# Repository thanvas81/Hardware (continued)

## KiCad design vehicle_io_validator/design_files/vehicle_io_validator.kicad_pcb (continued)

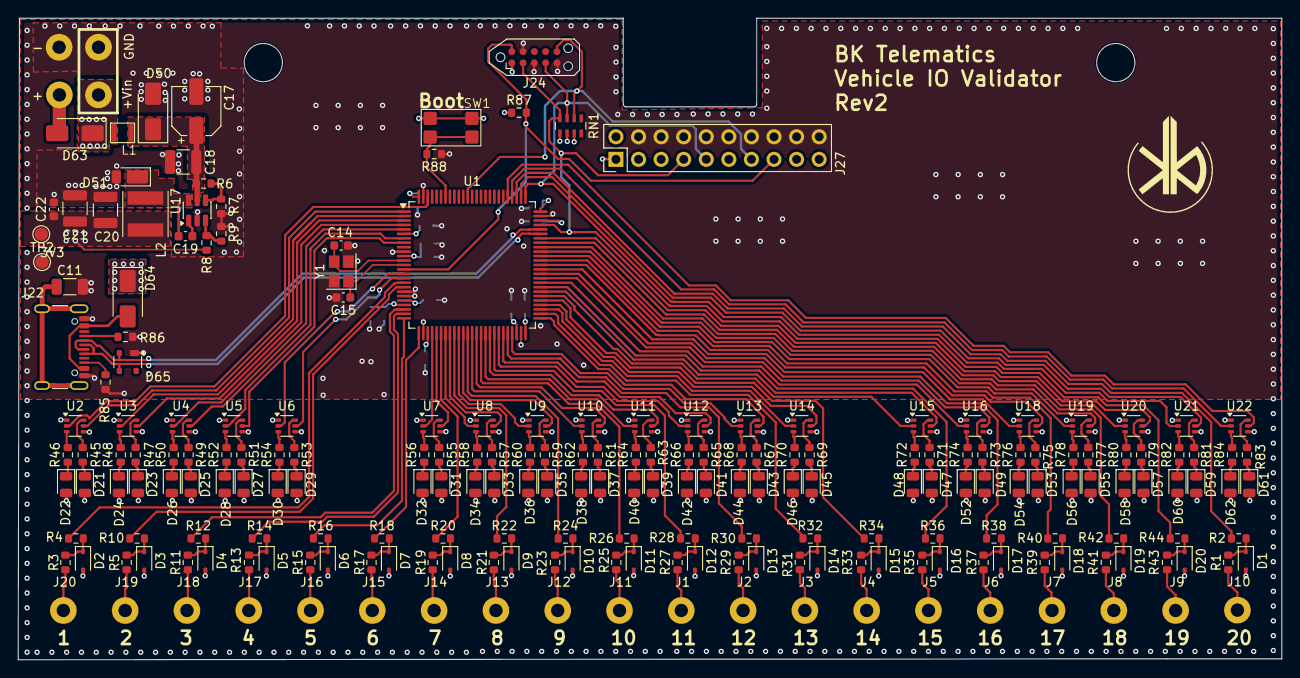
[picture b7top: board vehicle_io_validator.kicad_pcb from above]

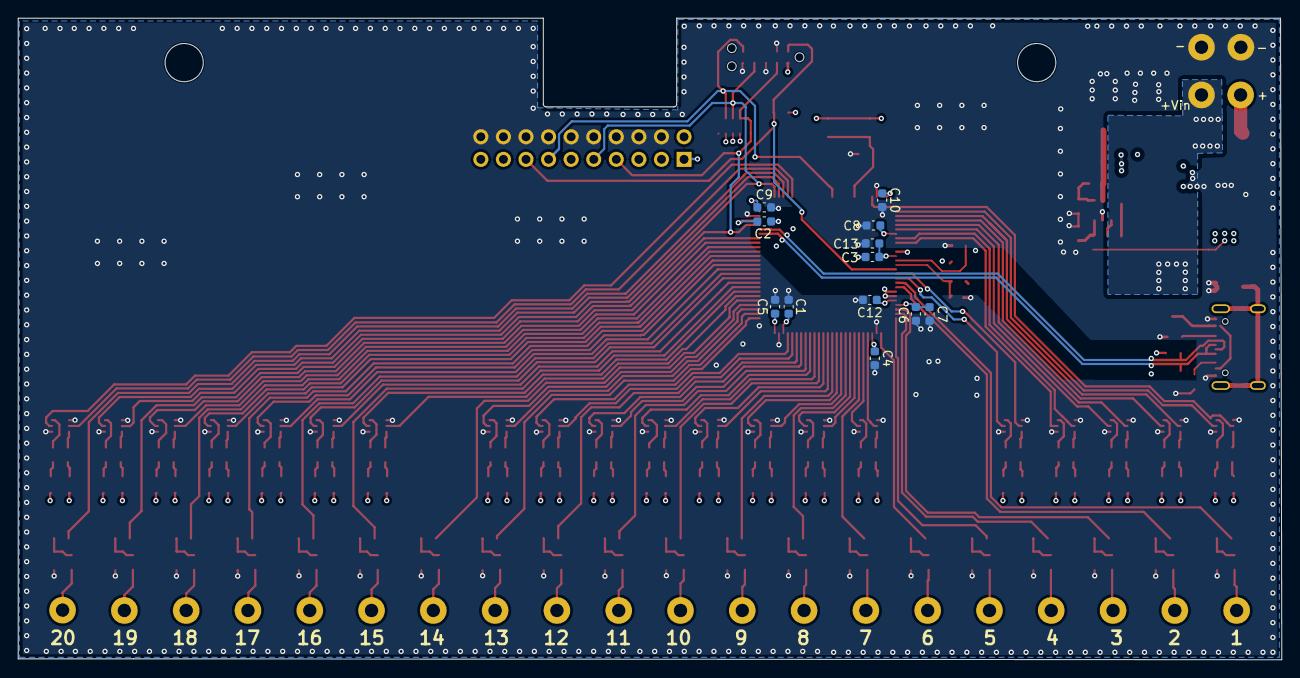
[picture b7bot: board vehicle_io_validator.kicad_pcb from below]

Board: 4 copper layers, 142.1 x 72.2 mm, 232 parts (12 on the bottom side), 201 nets.

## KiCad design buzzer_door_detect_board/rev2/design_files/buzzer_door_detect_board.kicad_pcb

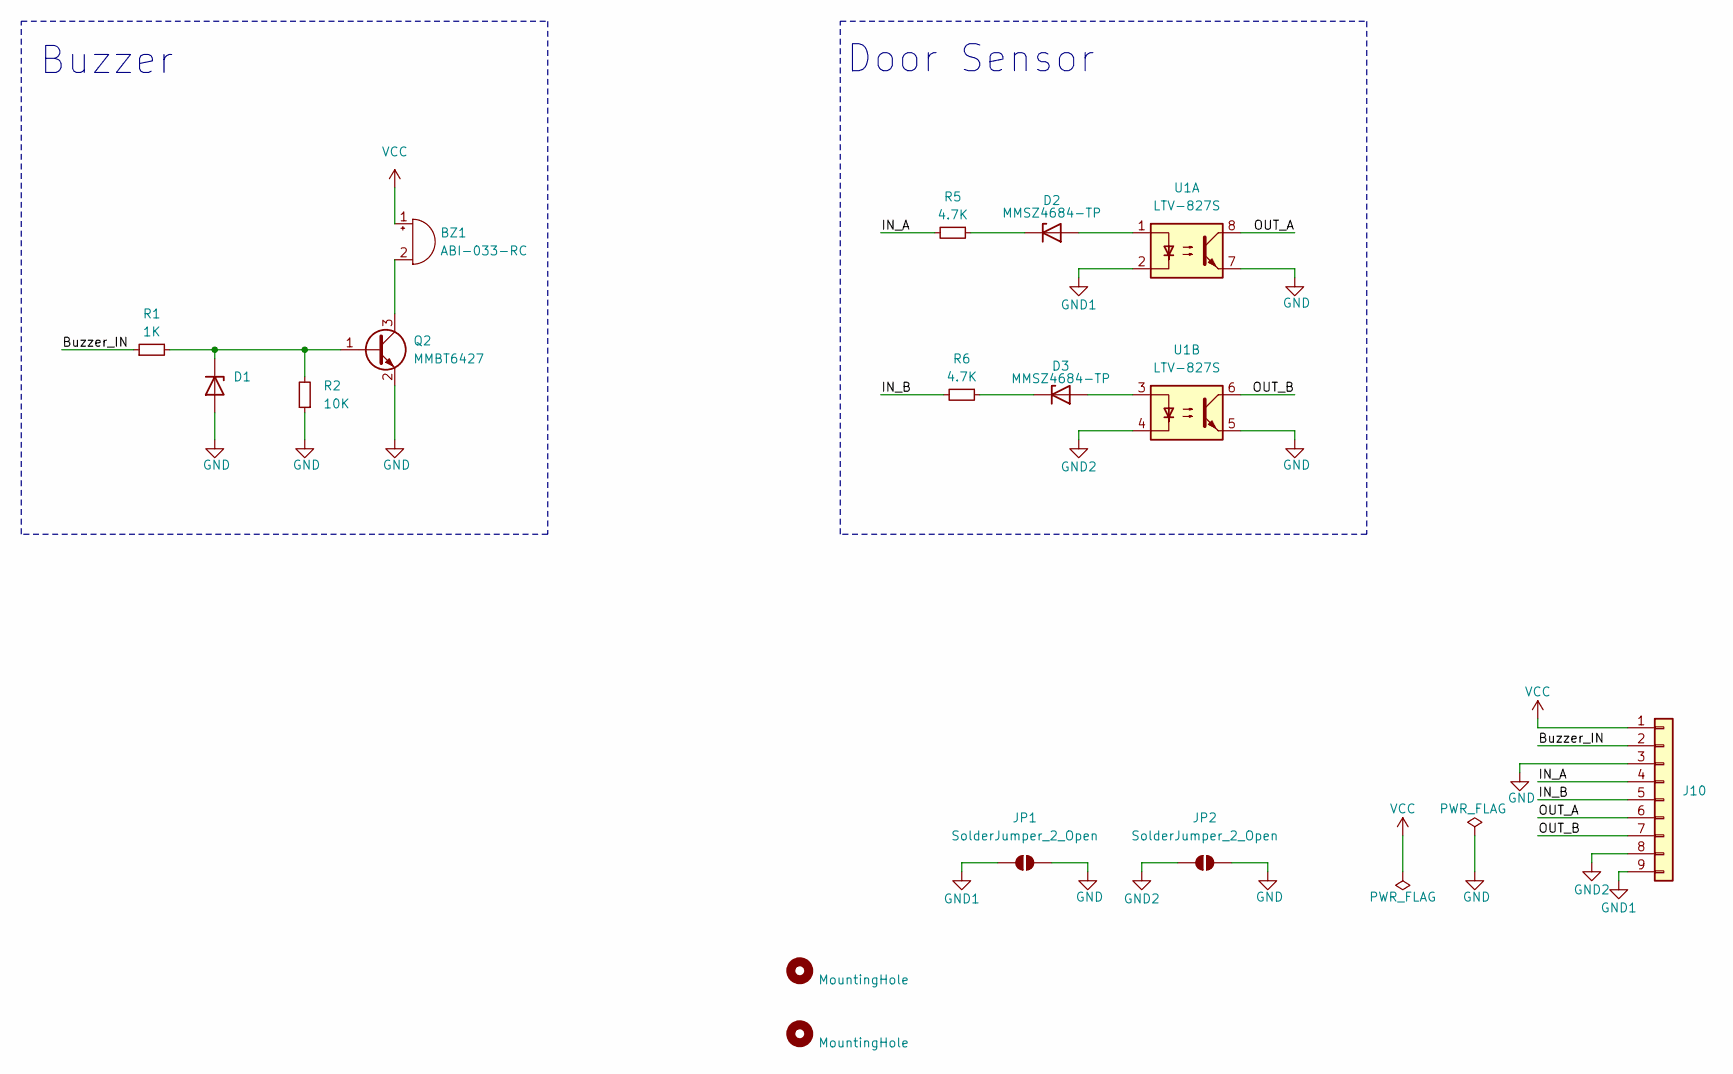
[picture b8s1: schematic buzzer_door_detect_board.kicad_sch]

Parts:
BZ1: ABI-033-RC
D1, D2, D3: MMSZ4684-TP; D_SOD-123
H1, H2: MountingHole; MountingHole_3.2mm_M3
J10: Conn_01x09; JST_ZH_B9B-ZR_1x09_P1.50mm_Vertical
JP1, JP2: SolderJumper_2_Open; SolderJumper-2_P1.3mm_Open_RoundedPad1.0x1.5mm
Q2: MMBT6427; SOT-23
R1: 1K; R_0805_2012Metric
R2: 10K; R_0805_2012Metric
R5, R6: 4.7K; R_0805_2012Metric
U1: LTV-827S; SMDIP-8_W9.53mm

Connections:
/Buzzer_IN: J10.2, R1.1
/IN_A: J10.4, R5.2
/IN_B: J10.5, R6.2
/OUT_A: J10.6, U1.8
/OUT_B: J10.7, U1.6
GND: D1.2 (A), J10.3, JP1.2 (B), JP2.2 (B), Q2.2 (E), R2.1, U1.5, U1.7
GND1: J10.9, JP1.1 (A), U1.2
GND2: J10.8, JP2.1 (A), U1.4
unnamed: BZ1.2 (-), Q2.3 (C)
unnamed: D1.1 (K), Q2.1 (B), R1.2, R2.2
unnamed: D2.2 (A), U1.1
unnamed: D2.1 (K), R5.1
unnamed: D3.2 (A), U1.3
unnamed: D3.1 (K), R6.1
VCC: BZ1.1 (+), J10.1

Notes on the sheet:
Door Sensor
Buzzer

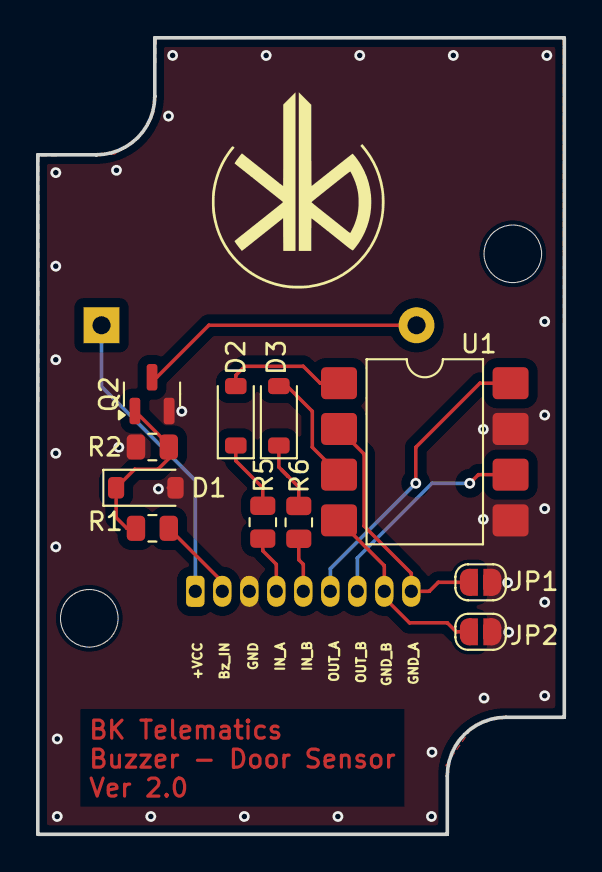
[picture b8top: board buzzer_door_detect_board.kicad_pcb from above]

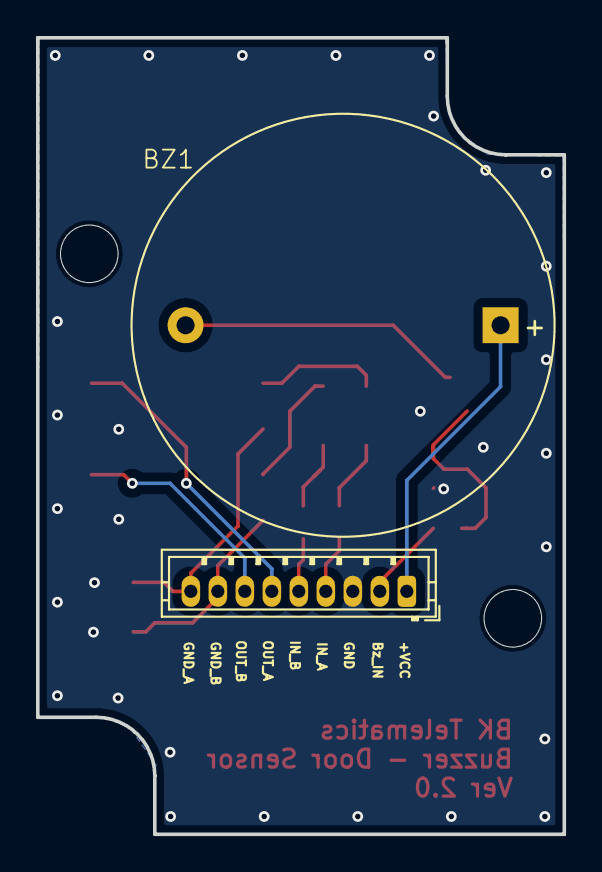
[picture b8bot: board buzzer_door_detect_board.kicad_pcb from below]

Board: 2 copper layers, 29.2 x 44.2 mm, 15 parts (2 on the bottom side), 15 nets.

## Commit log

2025-11-30 added hw folders
2025-11-30 removed some files
2025-11-30 Add rfid_rpi_hat project
2025-11-30 added one project
2025-11-30 Add README for embedded systems design
    This README.md file introduces a portfolio of embedded systems and electronics design projects, detailing the repository structure, technologies used, and contact information.
